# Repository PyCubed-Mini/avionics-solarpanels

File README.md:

# SatelliteHardware
PyCubedMini Core Satellite Hardware

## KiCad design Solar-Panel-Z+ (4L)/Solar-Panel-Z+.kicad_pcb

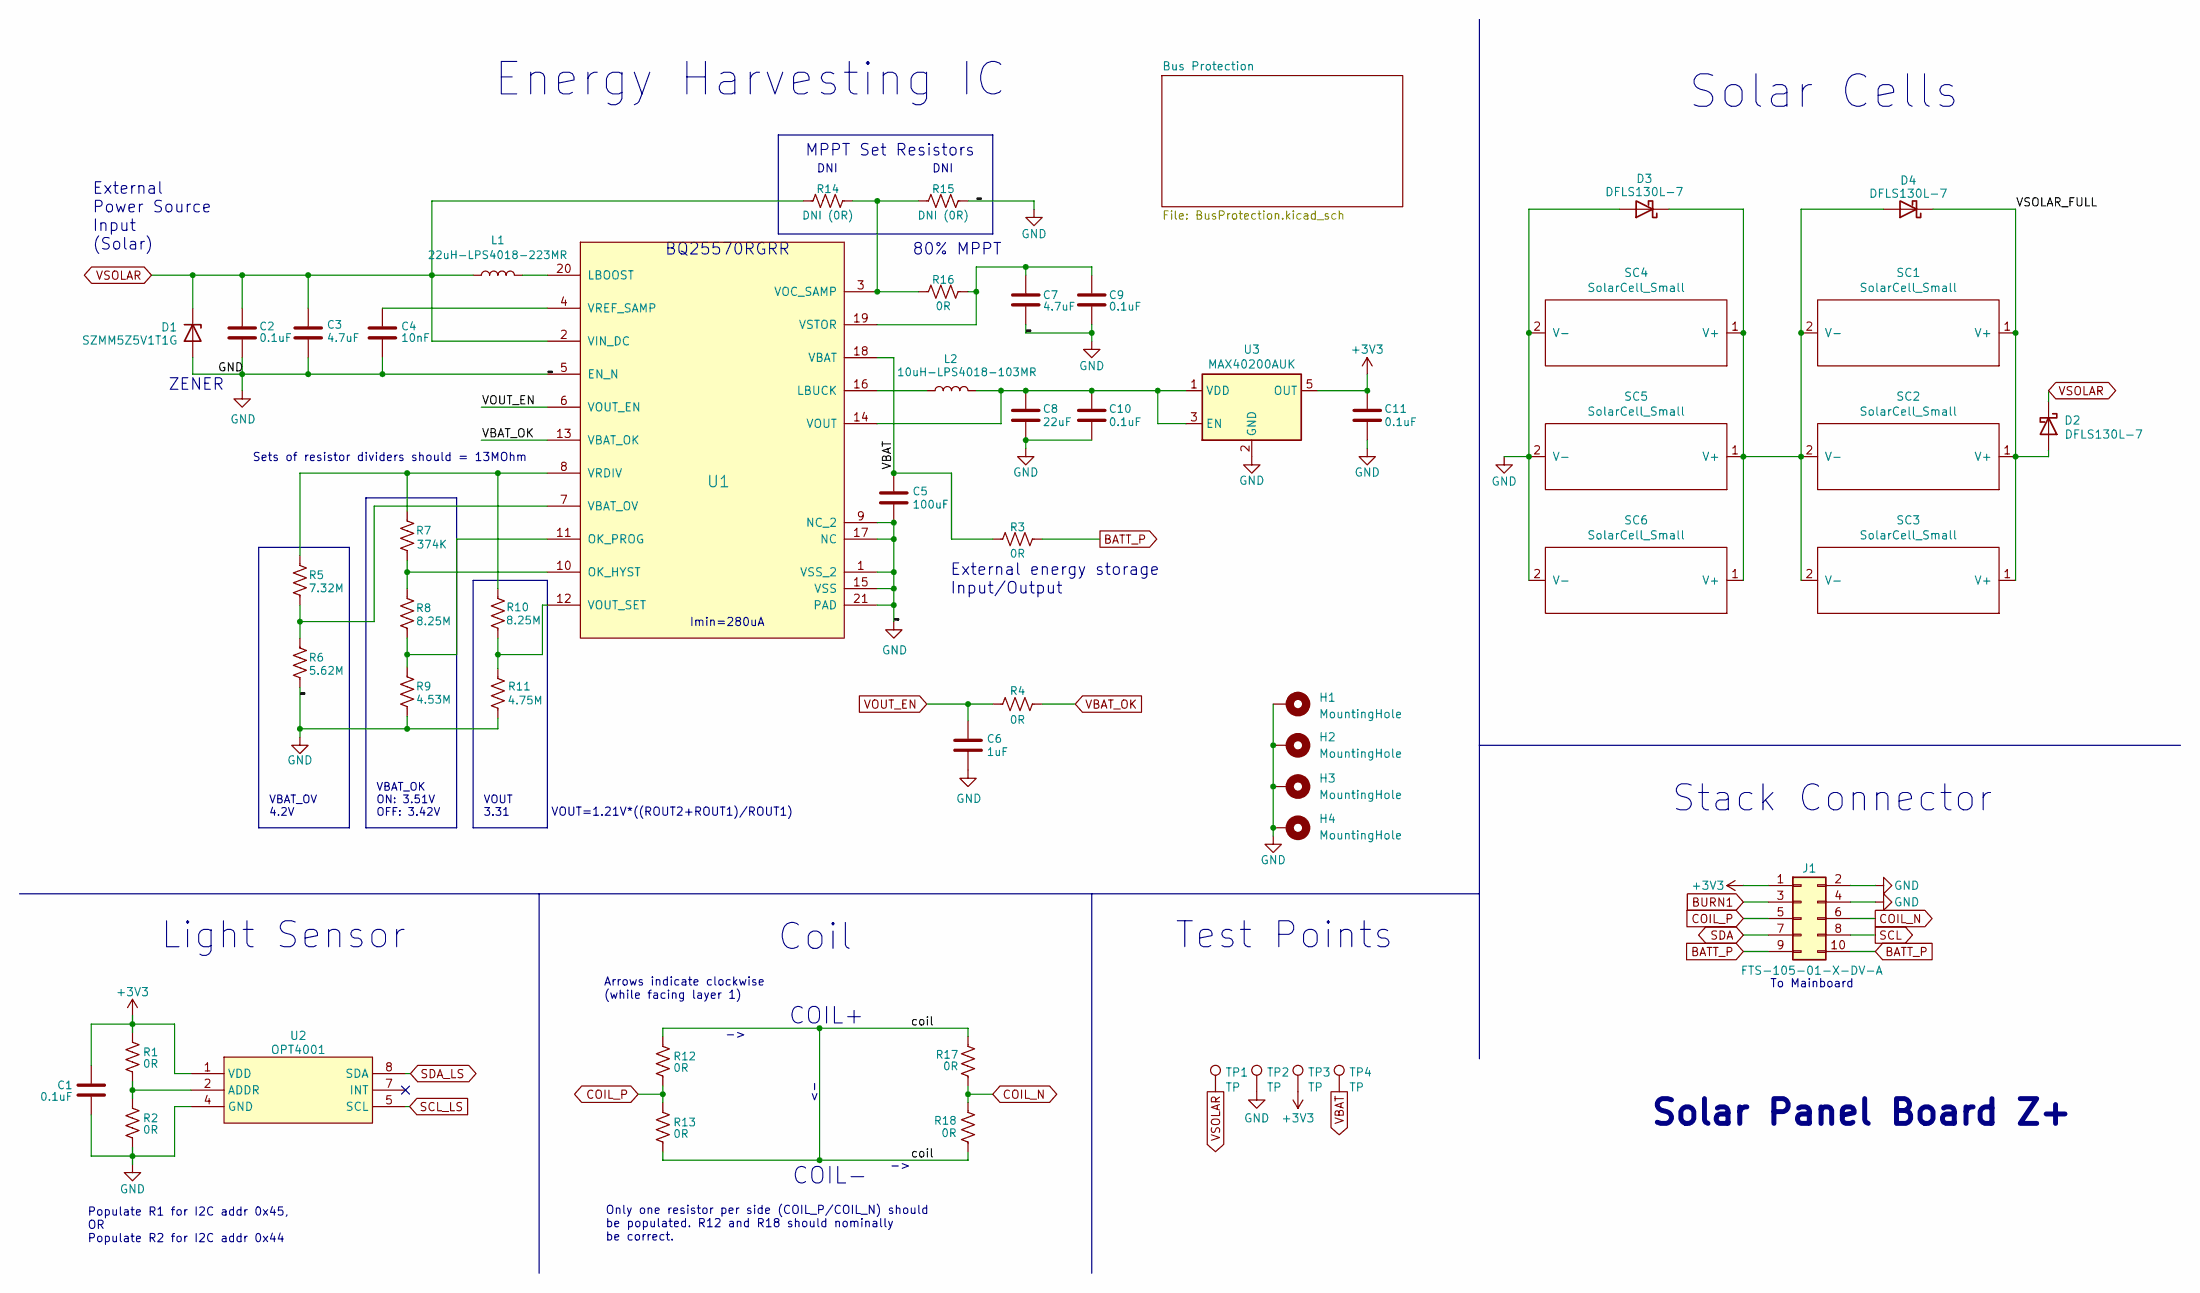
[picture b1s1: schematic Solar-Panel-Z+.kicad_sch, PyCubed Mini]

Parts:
C1: 0.1uF; C_0402_1005Metric
C2, C9, C10, C11: 0.1uF; C_0603_1608Metric
C3, C7: 4.7uF; C_0603_1608Metric
C4: 10nF; C_0603_1608Metric
C5: 100uF; C_0805_2012Metric
C6: 1uF; C_0603_1608Metric
C8: 22uF; C_0603_1608Metric
D1: SZMM5Z5V1T1G; D_SOD-523
D2, D3, D4: DFLS130L-7; D_PowerDI-123
H1, H2, H3, H4: MountingHole; MountingHole_2.2mm_M2_DIN965_Pad_TopBottom
J1: FTS-105-01-X-DV-A; SAMTEC-FTS-105-01-X-DV-A
L1: 22uH-LPS4018-223MR; LPS4018
L2: 10uH-LPS4018-103MR; LPS4018
R1, R2: 0R; R_0402_1005Metric
R3, R4, R12, R13, R16, R17, R18: 0R; R_0603_1608Metric
R5: 7.32M; R_0603_1608Metric
R6: 5.62M; R_0603_1608Metric
R7: 374K; R_0603_1608Metric
R8, R10: 8.25M; R_0603_1608Metric
R9: 4.53M; R_0603_1608Metric
R11: 4.75M; R_0603_1608Metric
R14, R15: DNI (0R); R_0603_1608Metric
SC1, SC2, SC3, SC4, SC5, SC6: SolarCell_Small; KXOB25-05X3F
TP1, TP2, TP3, TP4: TP; TestPoint_THTPad_D1.0mm_Drill0.5mm
U1: BQ25570RGRR; QFN50P350X350X100-21N-D
U2: OPT4001; SOT-583-8
U3: MAX40200AUK; SOT-23-5

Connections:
+3V3: C1.2, C11.1, J1.1, R1.2, TP3.1, U2.1 (VDD), U3.5 (OUT); also elsewhere on the board
/VSOLAR_FULL: D2.2 (A), D4.1 (K), SC1.1 (V+), SC2.1 (V+), SC3.1 (V+)
/coil: R12.2, R13.1, R17.2, R18.1
BATT_P: J1.9, J1.10, R3.1
BURN1: J1.3
COIL_N: J1.6, R17.1, R18.2
COIL_P: J1.5, R12.1, R13.2
GND: C1.1, C2.2, C3.2, C4.2, C5.2, C6.2, C7.2, C8.2, C9.2, C10.2, C11.2, D1.2 (A), D3.2 (A), H1.1, H2.1, H3.1, H4.1, J1.2, J1.4, R2.1, R6.1, R9.1, R11.1, R15.1, SC4.2 (V-), SC5.2 (V-), SC6.2 (V-), TP2.1, U1.1 (VSS_2), U1.5 (EN_N), U1.9 (NC_2), U1.15 (VSS), U1.17 (NC), U1.21 (PAD), U2.4 (GND), U3.2 (GND); also elsewhere on the board
unnamed: D3.1 (K), D4.2 (A), SC1.2 (V-), SC2.2 (V-), SC3.2 (V-), SC4.1 (V+), SC5.1 (V+), SC6.1 (V+)
unnamed: L1.2, U1.20 (LBOOST)
unnamed: L2.1, U1.16 (LBUCK)
unnamed: R7.1, R8.2, U1.10 (OK_HYST)
unnamed: R8.1, R9.2, U1.11 (OK_PROG)
unnamed: R5.1, R6.2, U1.7 (VBAT_OV)
unnamed: R14.1, R15.2, R16.2, U1.3 (VOC_SAMP)
unnamed: C8.1, C10.1, L2.2, U1.14 (VOUT), U3.1 (VDD), U3.3 (EN)
unnamed: R10.1, R11.2, U1.12 (VOUT_SET)
unnamed: R5.2, R7.2, R10.2, U1.8 (VRDIV)
unnamed: C4.1, U1.4 (VREF_SAMP)
unnamed: C7.1, C9.1, R16.1, U1.19 (VSTOR)
unnamed: R1.1, R2.2, U2.2 (ADDR)
SCL: J1.8; also elsewhere on the board
SCL_LS: U2.5 (SCL); also elsewhere on the board
SDA: J1.7; also elsewhere on the board
SDA_LS: U2.8 (SDA); also elsewhere on the board
VBAT: C5.1, R3.2, TP4.1, U1.18 (VBAT)
VBAT_OK: R4.1, U1.13 (VBAT_OK)
VOUT_EN: C6.1, R4.2, U1.6 (VOUT_EN)
VSOLAR: C2.1, C3.1, D1.1 (K), D2.1 (K), L1.1, R14.2, TP1.1, U1.2 (VIN_DC)

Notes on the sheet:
80% MPPT
DNI
Populate R1 for I2C addr 0x45, OR Populate R2 for I2C addr 0x44
Solar Cells
External Power Source Input (Solar)
Only one resistor per side (COIL_P/COIL_N) should be populated. R12 and R18 should nominally be correct.
Stack Connector
VOUT 3.31
Energy Harvesting IC
MPPT Set Resistors
Arrows indicate clockwise (while facing layer 1)
To Mainboard
Test Points
External energy storage Input/Output
COIL+
BQ25570RGRR
Light Sensor
Solar Panel Board Z+
VOUT=1.21V*((ROUT2+ROUT1)/ROUT1)
VBAT_OV 4.2V
VBAT_OK ON: 3.51V OFF: 3.42V
COIL-
Sets of resistor dividers should = 13MOhm
Imin=280uA
ZENER
Coil

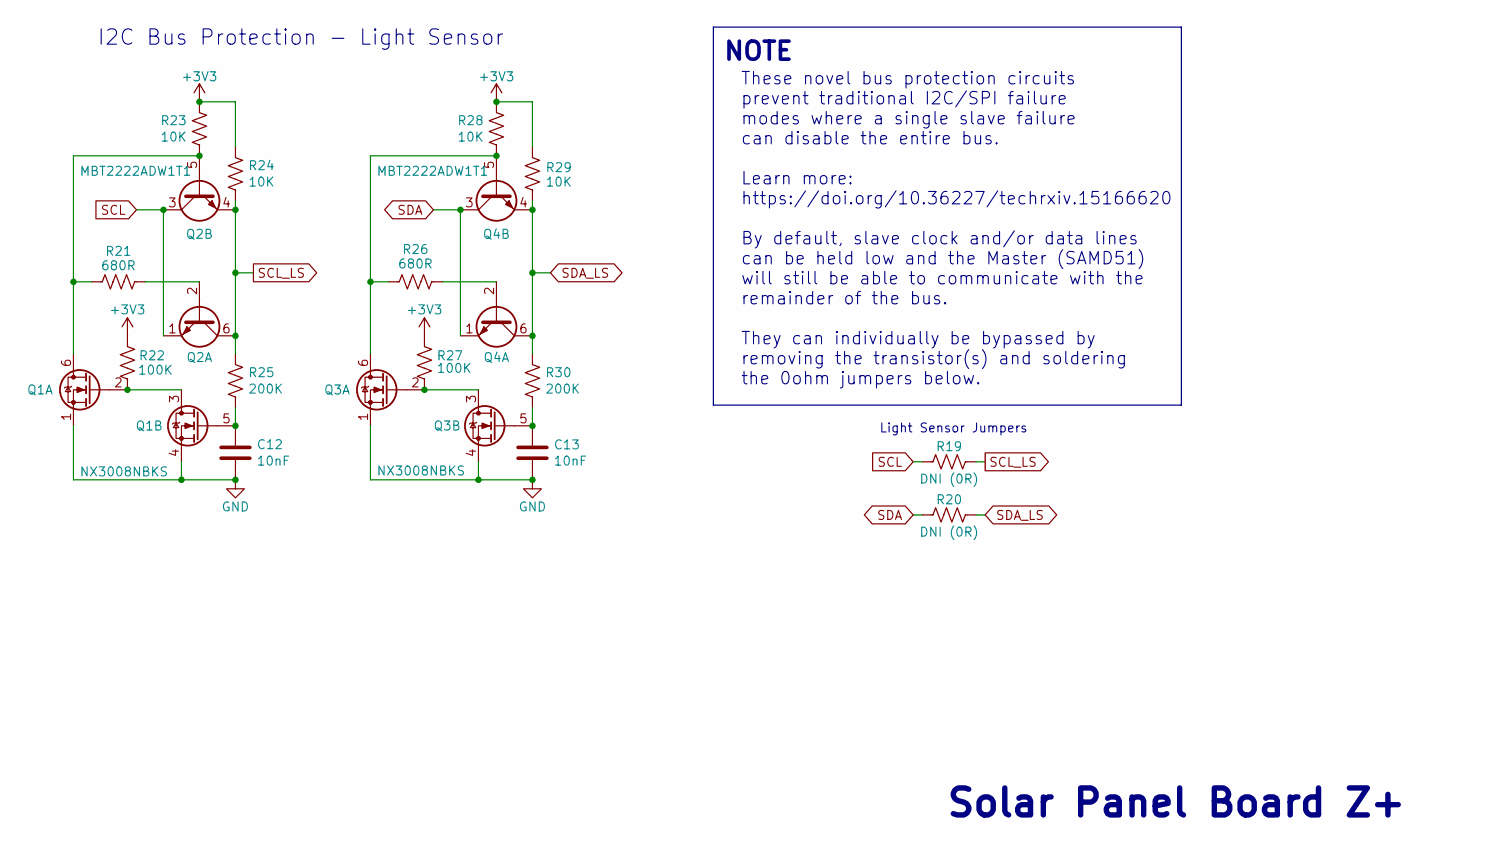
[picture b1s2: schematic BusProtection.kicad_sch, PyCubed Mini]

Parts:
C12, C13: 10nF; C_0603_1608Metric
Q1, Q3: NX3008NBKS; SOT-363_SC-70-6; Manufacturer_Part_Number NX3008NBKS
Q2, Q4: MBT2222ADW1T1; SOT-363_SC-70-6; Manufacturer_Part_Number MBT2222ADW1T1G
R19, R20: DNI (0R); R_0603_1608Metric
R21, R26: 680R; R_0603_1608Metric
R22, R27: 100K; R_0603_1608Metric
R23, R24, R28, R29: 10K; R_0603_1608Metric
R25, R30: 200K; R_0603_1608Metric

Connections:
+3V3: R22.1, R23.1, R24.1, R27.1, R28.1, R29.1; also elsewhere on the board
GND: C12.2, C13.2, Q1.1 (S2), Q1.4 (S1), Q3.1 (S2), Q3.4 (S1); also elsewhere on the board
unnamed: Q1.6 (D1), Q2.5 (B2), R21.2, R23.2
unnamed: Q1.2 (G2), Q1.3 (D2), R22.2
unnamed: C12.1, Q1.5 (G1), R25.2
unnamed: Q2.2 (B1), R21.1
unnamed: Q3.6 (D1), Q4.5 (B2), R26.2, R28.2
unnamed: Q3.2 (G2), Q3.3 (D2), R27.2
unnamed: C13.1, Q3.5 (G1), R30.2
unnamed: Q4.2 (B1), R26.1
SCL: Q2.1 (E1), Q2.3 (C2), R19.2; also elsewhere on the board
SCL_LS: Q2.4 (E2), Q2.6 (C1), R19.1, R24.2, R25.1; also elsewhere on the board
SDA: Q4.1 (E1), Q4.3 (C2), R20.2; also elsewhere on the board
SDA_LS: Q4.4 (E2), Q4.6 (C1), R20.1, R29.2, R30.1; also elsewhere on the board

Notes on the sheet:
Light Sensor Jumpers
These novel bus protection circuits prevent traditional I2C/SPI failure modes where a single slave failure can disable the entire bus. Learn more: https://doi.org/10.36227/techrxiv.15166620 By default, slave clock and/or data lines can be held low and the Master (SAMD51) will still be able to commu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
NOTE
I2C Bus Protection - Light Sensor
Solar Panel Board Z+

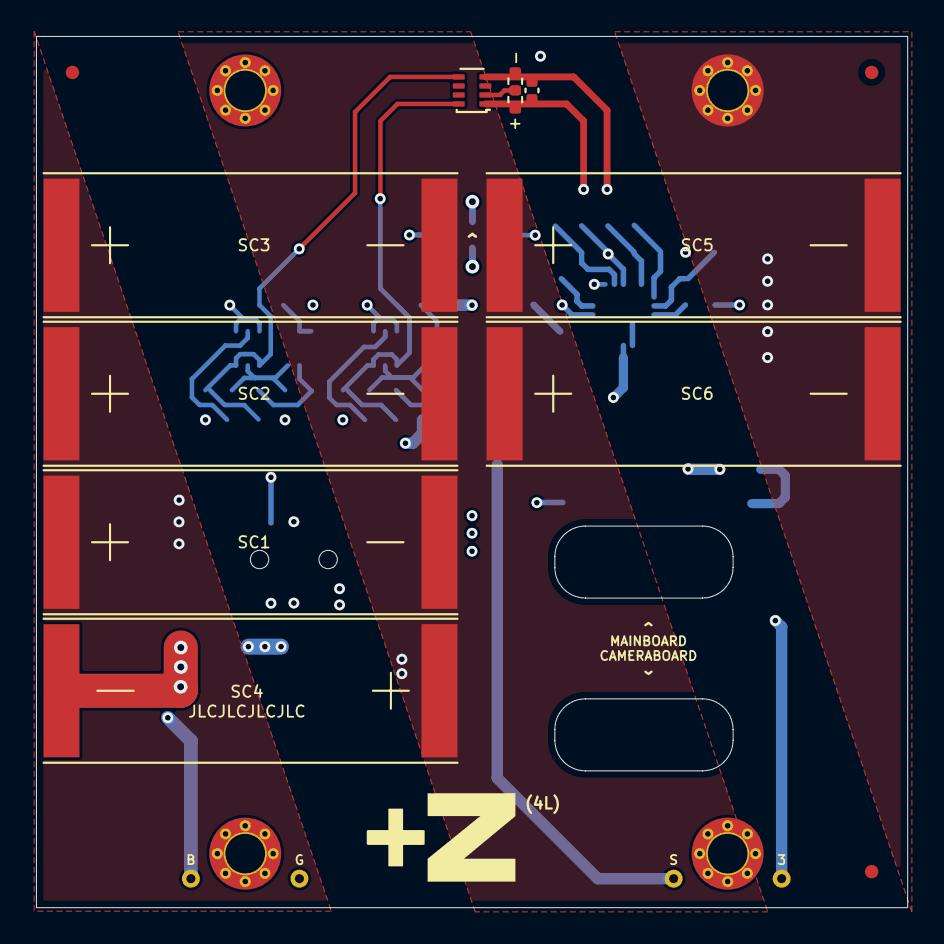
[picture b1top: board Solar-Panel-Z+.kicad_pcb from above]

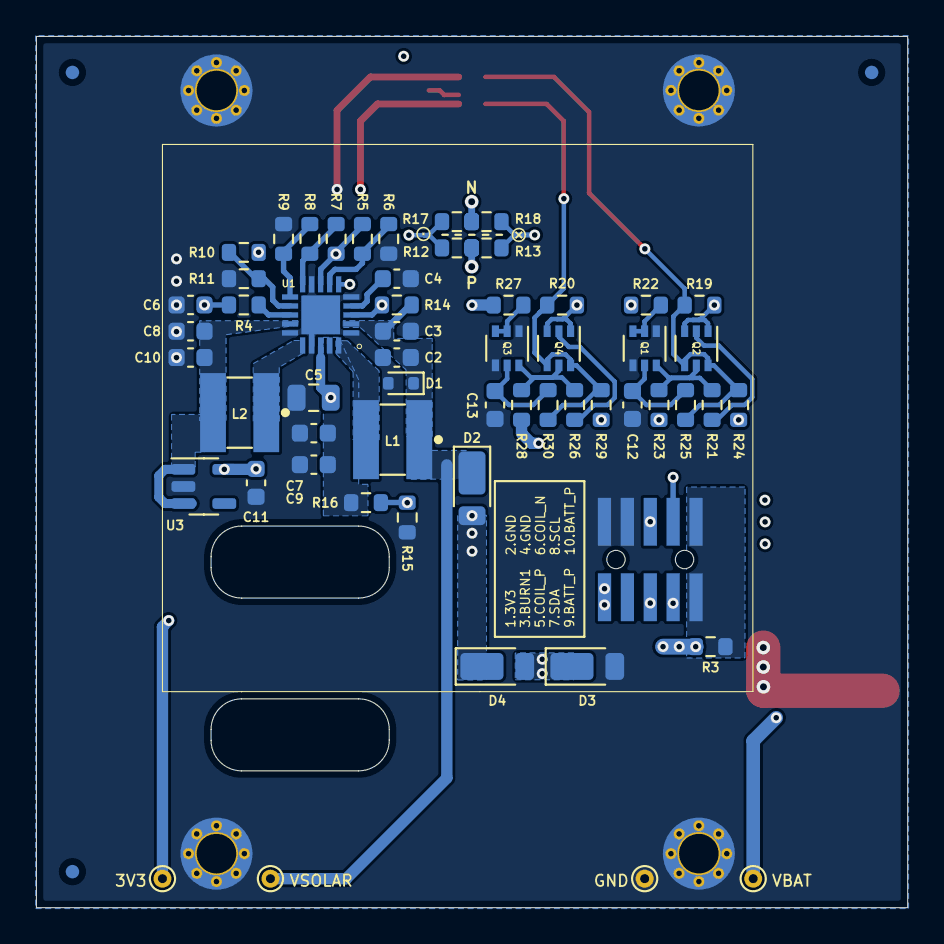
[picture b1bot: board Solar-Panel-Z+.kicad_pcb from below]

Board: 4 copper layers, 48.4 x 48.4 mm, 73 parts (58 on the bottom side), 36 nets.

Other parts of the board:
Ref**: Val**; ypanel
Ref**#2: Val**; pycubed_mini_half

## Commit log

2022-02-14 Solar-Panel--Y
    Adding cloned folder to Hardware Repository
2022-02-14 Adding Solar Panel Minus and Plus Y Directories
    Cloned Original Folders
2022-02-14 Adding Solar Panel X and Z Directories
    Cloned Original Repositories
2022-02-14 Double Committed Solar Panel Minus Y Directory
2022-02-14 Adding Solar Panel X
    Cloned Original Repository
    * removed archives from this commit because the number of files was too large. Will make another commit to add these
2022-02-14 Solar Panel X Archives 1/5
    ** not added in the last commit due to a limit on the number of files that can be committed at once
2022-02-14 Solar Panel X Archives 2/5
    ** not added in the last commit due to a limit on the number of files that can be committed at once
2022-02-14 Incorrect Directory
2022-02-14 Adding Archive Folder
    1/5
    ** not added in the last commit due to a limit on the number of files that can be committed at once
2022-02-14 Adding Archive Folders
    2/5
    ** not added in the last commit due to a limit on the number of files that can be committed at once
2022-02-14 Adding Archive Folder
    3/5
    ** not added in the last commit due to a limit on the number of files that can be committed at once
2022-02-14 Adding Archive Folders
    4/5
    ** not added in the last commit due to a limit on the number of files that can be committed at once
2022-02-14 Adding Archive Folder
    5/5
    ** not added in the last commit due to a limit on the number of files that can be committed at once
2022-02-16 Unnecessary
    Can access original solar panel X repository if we need to access these files.
2022-02-20 -Y Board Changes
2022-02-20 Added missing caps and fixed manufacturing error
2022-02-24 More Cleanup
2022-02-26 Finished Cleanup
2022-02-28 Moved board connectors to North board edges
2022-02-28 Added JLC order number silkscreen
2022-03-04 Solar Panel Keepouts
2022-03-06 Made Requested Changes
2022-03-06 Removed .kicad_prl Files
2022-03-06 Removed *.kicad_prl files
2022-03-08 Done with X, +/-Y, and +Z. TODO: -Z
2022-03-10 -Z board changes
2022-03-14 Cleaned up, exported step files
2022-03-16 Exported Gerbers
2022-06-14 Stack architecture schematic updates / fixes
2022-06-21 X board updates
2022-06-21 Added new keepouts
2022-06-21 Added extra area for keep in zones
2022-06-29 X / Y+ board updates v04
2022-06-29 Re-check boards, fixed connector pinouts, moved Y+ connector, re-export models
2022-06-30 X Board Changes for new Y rails
2022-06-30 New X panel keepout
2022-06-30 new keepout
2022-07-01 New X board keepouts
2022-07-01 Re-distribute buses between layers
2022-07-04 Finished Y- Board
2022-07-05 added X/Z board widths to keepout
2022-07-05 Z board keepouts
2022-07-05 standardized keepout naming
2022-07-05 Made Suggested Y- changes
2022-07-05 Moved Charging connector, added text
2022-07-05 New Y- Layout
2022-07-05 Ran KiCad Cleanup
2022-07-06 Modified coil resistor layout on X board
2022-07-06 cleanup on X
2022-07-06 Modified coil resistors to allow only one to be populated
2022-07-06 Modified coil resistors on Y- board
2022-07-06 Copper Fill cutouts on all layers
2022-07-06 Export New Gerbers
2022-07-17 Correct positions for everything except coils
2022-07-17 Added new edge cuts and connector
2022-07-17 Retracing coils
2022-07-18 added 3d models to fix paths
2022-07-18 copied over top layer pieces
2022-07-20 Added kicad libs
2022-07-20 Added new submodules
2022-07-21 Copied more of previous board
2022-08-06 Added 4 Layer Z+ board
2022-08-06 Added 4 Layer Z- board
2022-08-08 Z board updates
2022-08-31 Removed submodule Solar-Panel-Z-/kicad-libs
2022-09-02 Finished Y- 4 Layer Board
2022-09-02 Library updates
2022-09-03 Z- board antenna updates
2022-09-05 Added New Z+ Solar Panels
2022-09-06 New Y- and Z- boards
2022-09-06 Resized Copper Pours
2022-09-08 Added antenna cable silkscreen lines
2022-09-08 Modify antenna silkscreen lines to make it match where the slot on the bottom battery board will go
2022-09-08 Widened Power Traces on Y- Boards
2022-09-13 Exported Files
2022-10-09 Moved Access Port for new USBC location
2022-10-09 Update kicad_libs
2022-11-09 Updated all solar panels to Rev B2/01 + Export STEP / BOM
2022-11-10 DFM updates and repositioned -Z mounting holes
2022-11-10 Export -Z Step
2022-11-11 Fix Rail Interference issues
2022-11-11 Export new STEP files
2022-11-11 Export Gerbers
2022-11-13 Finish 6 Layer panel versions
2022-12-01 Stuff
2023-02-11 Changed design to TSL2691 and IRF7404 on Z- (4L)
2023-02-18 Changed TSL2591 to BH1750
    All boards (4L) except -Y
2023-02-19 Y- board changes for Rev B3/01
2023-02-25 Updated light sensor to OPT 3001, Updated solar diodes.
2023-02-25 Silkscreen fix for -Z antenna wire
2023-02-25 More silkscreen cleanup
2023-02-26 Removed gerbers from repo
2023-03-16 Updated Mounting Holes
2023-04-27 B3/02 Updates
2023-04-27 Minor Fixes
2023-04-30 Minor placement updates on -Y board
2023-05-28 Upload tester files
2023-05-28 Updated Sun Sensor to OPT4001
2023-05-28 Pulled tester lib models
2023-06-19 Moved -Y switches out 1mm
2023-06-19 Updated Rev to B3/03
2023-06-19 Pull kicad-libs
2023-06-21 Exported stuff
